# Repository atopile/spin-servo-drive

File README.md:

# Servos are dope.

Compared to the steppers we stick on our 3D printers, CNC machines and paintball turrets:
 - They're way faster 🏃
 - Far more powerful (higher torque for longer) 💪
 - More accurate (higher resolution) 🎯
 - And they're closed loop (they know where they are) 🤖

The only downside is that they're expensive, like hundreds of dollars.

Introducing spin ✨ - the $30 servo for the masses (designed with atopile)

## Wiggle wiggle wiggle

## Build your own Spin Servo Motor Drive

This project is fully open source and designed with [atopile](https://github.com/atopile/atopile), a new language and compiler to design electronics with code.

## Goals + (default) Specs

- Obviously better option than stepper motors for 3D printers, CNC machines and robotics
- Open-source design that is easy to:
  - contribute to
  - fork maintainable derivatives of
  - robust

- 2x CAN comms with JST-GH connectors
- XT30 power connector
- 0.25Nm continuous rated torque (0.75Nm peak)
- <0.1° resolution
- 12V-24V input voltage

## Getting started

This project was written in `ato`, a new electronics description language we are developing to help create and share electronic designs. Get started here: https://atopile.io/

### Electronics

**Write me please!**

### Firmware

Install [PlatformIO](https://platformio.org/) into VSCode. It has the utilities to build, upload and debug the firmware.

You may also need to install `libusb` (eg. `brew install libusb` on OSx) to run the build!

There are a few build configurations:
- `debug` is intended as a JTAG configuration and includes symbols to run the debugger.
- `dfu-manual` uses the GNU command-line dfu-utility to trigger the upload via USB (**Recommended USB workflow**)
- `dfu` uses the built-in PlatformIO dfu utility to program via USB (which **I struggled with on OSx**)

To run a build either use the sidebar (easiest IMO) or PlatformIO CLI (`pio run --help`).

#### Side-bar

#### CLI

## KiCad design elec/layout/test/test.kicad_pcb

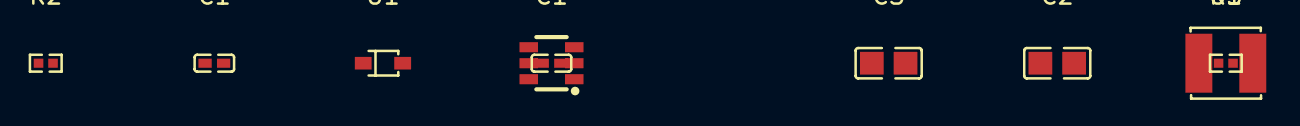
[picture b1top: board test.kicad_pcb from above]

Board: 2 copper layers, 9 parts (0 on the bottom side), 7 nets, no tracks yet.

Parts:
C1: 1µF ±10% 25V X5R; C0402-b3ef17
C1#2: 470nF ±20% 16V X5R; C0402-b3ef17
C2, C3: 10µF ±10% 25V X5R; C0805-3b2e55
R1: 7.5kΩ ±1% 62.5mW; R0402-56259e
R2: 24kΩ ±1% 62.5mW; R0402-56259e
U1: SOD-323_L1.8-W1.3-LS2.5-RD
U2: SOT-23-6_L2.9-W1.6-P0.95-LS2.8-BR
U3: 10µH ±20%; IND-SMD_L4.0-W4.0

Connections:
CB: C1#2.1, U2.1
cathode: C1#2.2, U1.1, U2.6, U3.1
gnd: C2.2, U2.2
gnd-1: C3.2, R1.2, U1.2
hv: C2.1, U2.4, U2.5
hv-1: C3.1, R2.1, U3.2
line: R1.1, R2.2, U2.3

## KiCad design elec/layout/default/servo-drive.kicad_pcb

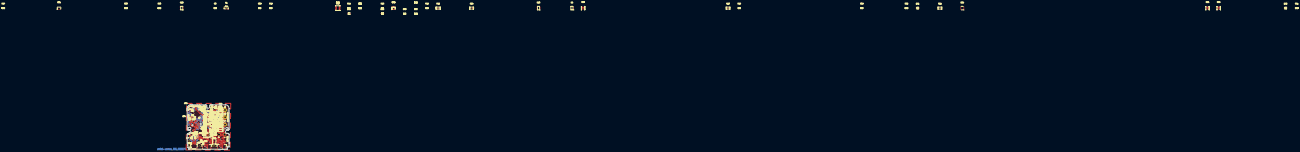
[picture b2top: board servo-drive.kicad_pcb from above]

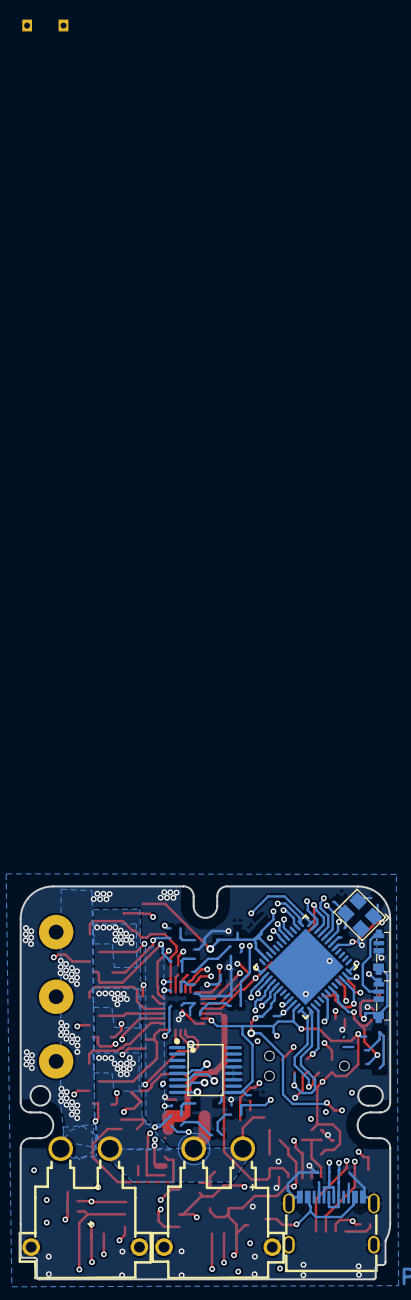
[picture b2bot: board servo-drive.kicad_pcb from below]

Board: 4 copper layers, 37.6 x 39.9 mm, 138 parts (8 on the bottom side), 80 nets.

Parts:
C2, C13, C16, C17, C18, C19, C28, C40, C51: 100nF ±10% 16V X7R; C0402-b3ef17
C3, C4, C6, C20, C21, C22, C25, C26, C27, C29, C30, C35, C36, C37, C38, C39, C47, C48, C49: 10µF ±10% 50V X5R; C0805-3b2e55
C7, C33, C34, C41, C43, C45, C50: 1µF ±10% 16V X5R; C0402-b3ef17
C10, C11, C12: 2.2nF ±10% 50V X7R; C0402-b3ef17
C23, C31, C32: 4.7µF ±10% 16V X5R; C0603-bd72f6
C42, C44: 20pF ±5% 50V C0G; C0402-b3ef17
DS1, DS2: Diode_1N5819WS; SOD-323_L1.8-W1.3-LS2.5-RD
DS1#2, DS2#2: SOD-323_L1.8-W1.3-LS2.5-RD
J1: USB-C-SMD_KH-TYPE-C-16P
R1, R10, R11, R15, R16, R20, R38, R46, R52: 10kΩ ±1% 62.5mW; R0402-56259e
R2, R6, R13, R25, R44, R48, R50: 1kΩ ±1% 62.5mW; R0402-56259e
R3: 100kΩ ±1% 62.5mW; R0402-56259e
R5, R9: 5.1kΩ ±1% 62.5mW; R0402-56259e
R7: 200Ω ±1% 62.5mW; R0402-56259e
R12, R14, R26, R45, R49, R51: 45.3kΩ ±1% 62.5mW; R0402-56259e
R31: 40.2kΩ ±1% 62.5mW; R0402-56259e
U1: KEY-SMD_SKTDLDE010
U2, U14: CONN-TH_XT30PW-M
U3: 10kΩ ±1% 62.5mW; R0402-56259e
U4, U6, U20, U23: SOT-23-5_L3.0-W1.7-P0.95-LS2.8-BR
U5, U32: LED-SMD_4P-L4.0-W1.4_SK6805SIDE-S
U7, U8, U9: OutputPad
U10, U21, U24: _DMT3009LDT_7; V-DFN3030-8K_L3.0-W3.0-P0.65-BL
U10#2, U21#2, U24#2: 3mΩ ±1% 500mW; R0805-c79e8b
U11, U22, U28: V-DFN3030-8K_L3.0-W3.0-P0.65-BL
U12: VQFN-24_L4.0-W4.0-P0.50-TL-EP2.5
U13: UFQFPN-48_L7.0-W7.0-P0.50-BL-EP
U15: CONN-SMD_4P-P1.00_SM04B-SRSS-TB-LF-SN
U16: TAG-CONNECT_TC2050-IDC
U17, U19, U31, U33, U34, U35: NetTie-2_SMD_Pad0.25mm
U18, U39: SOT-23-6_L2.9-W1.6-P0.95-LS2.8-BR
U25: SOIC-8_L4.9-W3.9-P1.27-LS6.0-BL
U26, U27: CONN-SMD_4P-P1.25_SM04B-GHS-TB-LF-SN
U29: TSSOP-16_L5.0-W4.4-P0.65-LS6.4-BL
U30: 470nF ±20% 16V X5R; C0402
U30#2: 470nF ±20% 16V X5R; C0402-b3ef17
U36, U38#2, U43#2, U44, U48, U49#2: 1kΩ ±1% 62.5mW; R0402-56259e
U37: OSC-SMD_4P-L3.2-W2.5-BL
U38, U43, U49: 10kΩ ±1% 62.5mW; R0402
U40: IND-SMD_L4.0-W4.0
U41: 4.7µF ±20% 6.3V X5R; C0402
U41#2: 2.2µF ±20% 6.3V X5R; C0402-b3ef17
U42: 10µF ±10% 25V X5R; C0805-3b2e55
U45, U47, U50#2, U52#2: 1µF ±10% 16V X5R; C0402-b3ef17
U46: _LDK220M_R; SOT-23-5_L3.0-W1.7-P0.95-LS2.8-BL
U46#2, U51: SOT-23-5_L3.0-W1.7-P0.95-LS2.8-BL
U50, U52: 1µF ±10% 16V X5R; C0402

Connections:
A5: J1.A5, R5.1
ADJ_NC: U48.1, U49#2.2, U51.4
B5: J1.B5, R9.1
CANH: U25.7, U26.2, U27.2
CANL: U25.6, U26.3, U27.3
CB: U30#2.1, U39.1
FB: U36.1, U38#2.2, U39.3
PF1_OSC_OUT: R7.1, U13.6
anchor: U1.3, U1.4
anode: DS2#2.2, J1.A4, J1.A9, J1.B4, J1.B9
cathode: DS1.1, DS1#2.1, U30.2, U30#2.2, U39.6, U40.1
cs: U13.25, U29.8
dm: J1.A7, J1.B7, U13.33
dp: J1.A6, J1.B6, U13.34
gnd: R26.2, R46.1, U20.4
gnd-1: R14.2, R45.2, R51.2, U4.3, U4.4
gnd-2: C2.2, C3.2, C4.2, C6.2, C7.2, C10.2, C11.2, C12.2, C13.2, C16.2, C17.2, C18.2, C19.2, C20.2, C21.2, C22.2, C23.2, C25.2, C26.2, C27.2, C28.2, C29.2, C30.2, C31.2, C32.2, C33.2, C34.2, C35.2, C36.2, C37.2, C38.2, C39.2, C40.2, C42.2, C44.2, C47.2, C48.2, C49.2, C50.2, C51.2, DS1.2, DS1#2.2, J1.1, J1.2, J1.3, J1.4, J1.A1, J1.A12, J1.B1, J1.B12, R2.2, R5.2, R9.2, R11.2, R20.1, R31.2, R38.2, U2.1, U2.3, U2.4, U3.2, U4.2, U5.2, U6.2, U10#2.2, U12.6, U12.25, U13.49, U14.1, U14.3, U14.4, U15.1, U15.5, U15.6, U16.3, U16.5, U18.2, U19.2, U20.2, U21#2.2, U23.2, U24#2.2, U25.2, U25.8, U26.4, U26.5, U26.6, U27.4, U27.5, U27.6, U29.4, U29.11, U29.12, U29.13, U32.2, U33.2, U35.2, U36.2, U37.2, U37.4, U39.2, U41.2, U41#2.2, U42.2, U43.2, U43#2.2, U45.2, U46.2, U46#2.2, U47.2, U48.2, U50.2, U50#2.2, U51.2, U52.2, U52#2.2
gnd-3: U10#2.1, U11.5, U11.6, U11.7, U17.2
gnd-4: R49.2, R52.1, U23.4
gnd-5: R12.2, R16.1, U6.4
gnd-6: U21#2.1, U22.5, U22.6, U22.7, U31.2
gnd-7: U24#2.1, U28.5, U28.6, U28.7, U34.2
hv: C7.1, C13.1, C16.1, C17.1, C18.1, C40.1, C50.1, C51.1, R1.1, R3.2, R15.1, U1.2, U4.5, U6.5, U12.5, U13.20, U13.21, U13.23, U13.35, U13.48, U15.2, U16.1, U18.5, U20.5, U23.5, U25.3, U29.9, U44.1, U46#2.5, U47.1
hv-1: C3.1, C4.1, C6.1, C20.1, C21.1, C22.1, C25.1, C26.1, C27.1, C29.1, C30.1, C35.1, C36.1, C37.1, C38.1, C39.1, C47.1, C48.1, C49.1, R10.1, U2.2, U11.2, U11.3, U11.4, U11.10, U14.2, U22.2, U22.3, U22.4, U22.10, U28.2, U28.3, U28.4, U28.10, U39.4, U39.5, U41#2.1
hv-2: C23.1, C31.1, C32.1, U12.4, U38#2.1, U40.2, U42.1, U50#2.1, U51.1, U51.3
hv-3: C33.1, C34.1, DS2#2.1, U5.1, U10.2, U10.3, U10.4, U10.10, U21.2, U21.3, U21.4, U21.10, U24.2, U24.3, U24.4, U24.10, U26.1, U27.1, U32.1, U41.1, U45.1, U46#2.1, U46#2.3, U49#2.1, U51.5, U52#2.1
inverting: R6.2, R12.1, U6.3
inverting-1: R48.2, R49.1, U23.3
inverting-2: R25.2, R26.1, U20.3
io: C28.1, R15.2, U3.1, U13.12
io-1: U12.10, U22.8
io-2: C43.2, U8.1, U12.15, U22.9
io-3: U12.1, U12.22, U13.8
ios-io: U5.3, U32.4
micro-io: R2.1, U13.46, U18.4
micro-io-2: R3.1, U13.14, U18.6
miso: U13.27, U29.5
mosi: U13.28, U29.6
non_inverting: C2.1, R1.2, R38.1, U4.1
non_inverting-1: R13.2, R14.1, U6.1
non_inverting-2: R44.2, R45.1, U20.1
non_inverting-3: R50.2, R51.1, U23.1
out: U43#2.1, U44.2, U46#2.4
power_stage.gate_driver-io: C45.1, U12.14
power_stage.gate_driver-io-1: R31.1, U12.21
power_stage.gate_driver-vcc: C43.1, U12.17
power_stage.gate_driver-vcc-1: C41.1, U12.20
power_stage.phase_a.current_sensor-top: R13.1, U17.1
power_stage.phase_a.current_sensor-top-1: R6.1, U19.1
power_stage.phase_b.current_sensor-top: R25.1, U33.1
power_stage.phase_b.current_sensor-top-1: R44.1, U31.1
power_stage.phase_c.current_sensor-top: R50.1, U34.1
power_stage.phase_c.current_sensor-top-1: R48.1, U35.1
reset: U13.7, U16.10
rx: U18.3, U25.4
sck: U13.26, U29.7
scl: U13.16, U15.4
sda: U13.30, U15.3
tck: U13.37, U16.4
tdi: U13.38, U16.8
tdo: U13.41, U16.6
tms: U13.36, U16.2
tx: U13.47, U25.1
vcc: U12.9, U28.8
vcc-1: U12.3, U12.24, U13.10
vcc-2: C41.2, U7.1, U11.9, U12.18
vcc-3: C12.1, R52.2, U13.11
vcc-4: U11.1, U12.19
vcc-5: U12.16, U22.1
vcc-6: U12.13, U28.1
vcc-7: U11.8, U12.11
vcc-8: C10.1, R16.2, U10.9, U13.17
vcc-9: R20.2, U1.1, U13.43, U18.1
vcc-10: C11.1, R46.2, U13.18
vcc-11: U12.2, U12.23, U13.9
vcc-12: C45.2, U9.1, U12.12, U28.9
vcc-13: C19.1, R10.2, R11.1, U13.13
vcc-14: U5.4, U13.29
xin: C42.1, U13.5, U37.1
xout: C44.1, R7.2, U37.3

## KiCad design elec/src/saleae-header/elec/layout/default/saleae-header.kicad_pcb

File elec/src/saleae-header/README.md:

# template

Project description goes here.

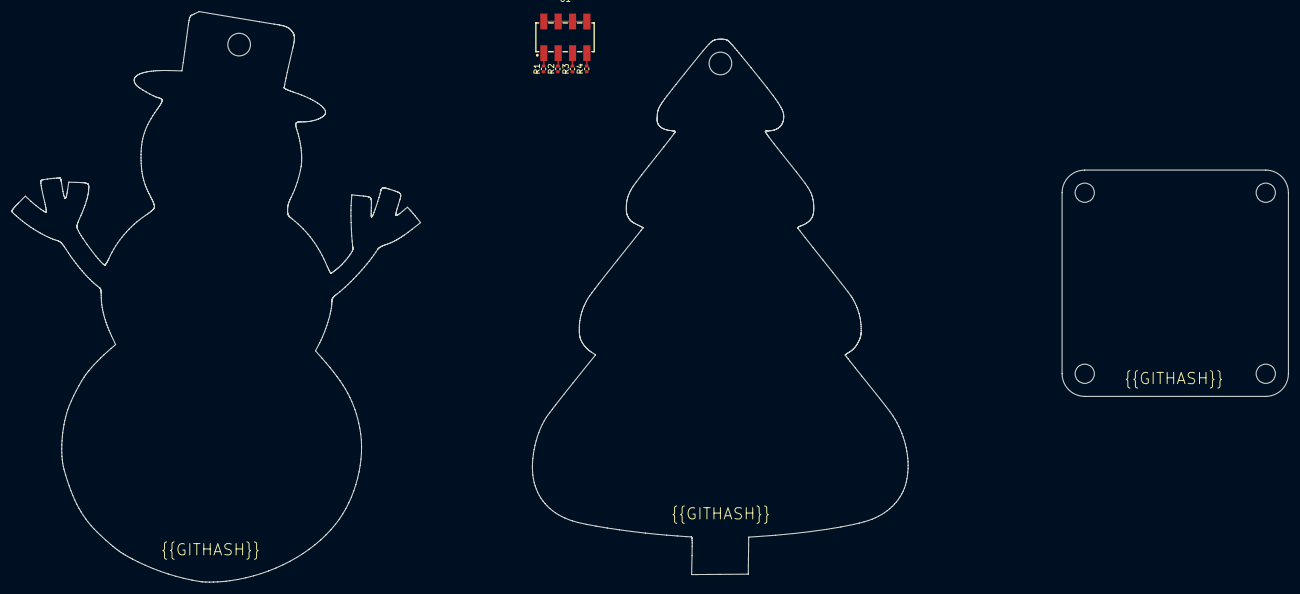
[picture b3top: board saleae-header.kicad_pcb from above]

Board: 2 copper layers, 66.4 x 94.6 mm, 5 parts (0 on the bottom side), 5 nets.

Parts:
R1, R2, R3, R4: Chip Resistor - Surface Mount 1KOhms ±5% 1/16W 04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; R0402
U1: HDR-SMD_8P-P2.54-V-M-R2-C4-LS7.4

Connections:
_1: R1.2, U1.1
_3: R2.2, U1.3
_5: R3.2, U1.5
_7: R4.2, U1.7
gnd: U1.2, U1.4, U1.6, U1.8

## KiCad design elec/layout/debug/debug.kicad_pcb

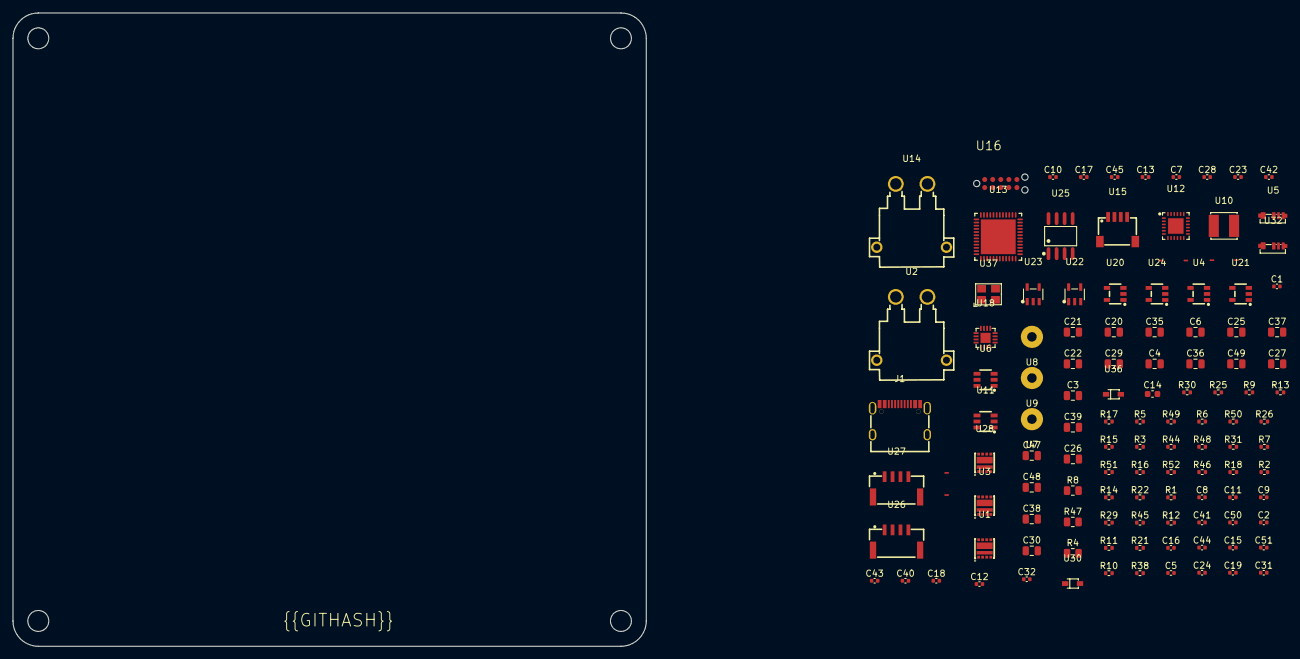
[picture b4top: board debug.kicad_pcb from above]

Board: 2 copper layers, 100.0 x 100.0 mm, 120 parts (0 on the bottom side), 75 nets, no tracks yet.

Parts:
C1, C5, C9, C15, C16, C18, C28, C31, C32, C41, C43, C45, C50: 25V 1uF X5R ±10% 0402 Multilayer Ceramic Capacito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; C0402
C2, C7, C13, C17, C19, C23, C40, C51: 16V 100nF X7R ±10% 0402 Multilayer Ceramic Capaci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; C0402
C3, C4, C6, C20, C21, C22, C25, C26, C27, C29, C30, C35, C36, C37, C38, C39, C47, C48, C49: C0805
C8: 6.3V 10uF X5R ±20% 0402 Multilayer Ceramic Capaci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; C0402
C10, C11, C12: 50V 2.2nF X7R ±10% 0402 Multilayer Ceramic Capaci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; C0402
C14: 50V 1uF X5R ±10% 0603 Multilayer Ceramic Capacito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; C0603
C24: 16V 220nF X7R ±10% 0402 Multilayer Ceramic Capaci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; C0402
C42, C44: 50V 20pF C0G ±5% 0402 Multilayer Ceramic Capacito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; C0402
J1: USB-C-SMD_KH-TYPE-C-16P
R1, R10, R11: 62.5mW ±1% ±200ppm/℃ 1.62kΩ 0402 Chip Resistor - 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; R0402
R2, R6, R13, R25, R44, R48, R50: 62.5mW Thick Film Resistors ±100ppm/℃ ±1% 1kΩ 040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; R0402
R3: 62.5mW Thick Film Resistors ±100ppm/℃ ±1% 100kΩ 0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; R0402
R4, R8, R47: R0805
R5, R9: 62.5mW Thick Film Resistors ±100ppm/℃ ±1% 5.1kΩ 0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; R0402
R7: 62.5mW Thick Film Resistors ±100ppm/℃ ±1% 220Ω 04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; R0402
R12, R14, R26, R45, R49, R51: 62.5mW Thick Film Resistors ±100ppm/℃ ±1% 47kΩ 04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; R0402
R15: 62.5mW Thick Film Resistors ±100ppm/℃ ±1% 10kΩ 04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; R0402
R16, R46, R52: 62.5mW ±1% ±200ppm/℃ 73.2Ω 0402 Chip Resistor - S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; R0402
R17: 62.5mW Thick Film Resistors ±100ppm/℃ ±1% 20.5kΩ 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; R0402
R18: 62.5mW Thick Film Resistors ±100ppm/℃ ±1% 6.34kΩ 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; R0402
R21: 62.5mW Thick Film Resistors ±100ppm/℃ ±1% 11.5kΩ 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; R0402
R22: 62.5mW Thick Film Resistors ±100ppm/℃ ±1% 6.19kΩ 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; R0402
R29: 62.5mW Thick Film Resistors ±100ppm/℃ ±1% 41.2kΩ 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; R0402
R30: 62.5mW Thick Film Resistors ±100ppm/℃ ±1% 4.32kΩ 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; R0402
R31: 62.5mW Thick Film Resistors ±100ppm/℃ ±1% 40.2kΩ 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; R0402
R38: 62.5mW Thick Film Resistors ±100ppm/℃ ±1% 1.54kΩ 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; R0402
U1, U3, U28: V-DFN3030-8K_L3.0-W3.0-P0.65-BL
U2, U14: CONN-TH_XT30PW-M
U4, U20, U21, U24: SOT-23-5_L3.0-W1.7-P0.95-LS2.8-BR
U5, U32: LED-SMD_4P-L4.0-W1.4_SK6805SIDE-S
U6, U11: SOT-23-6_L2.9-W1.6-P0.95-LS2.8-BR
U7, U8, U9: OutputPad
U10: IND-SMD_L4.0-W4.0
U12: VQFN-24_L4.0-W4.0-P0.50-TL-EP2.5
U13: UFQFPN-48_L7.0-W7.0-P0.50-BL-EP
U15: CONN-SMD_4P-P1.00_SM04B-SRSS-TB-LF-SN
U16: TAG-CONNECT_TC2050-IDC
U17, U19, U31, U33, U34, U35: NetTie-2_SMD_Pad0.25mm
U18: VQFN-16_L3.0-W3.0-P0.50-BL-EP1.6
U22, U23: SOT-23-5_L3.0-W1.7-P0.95-LS2.8-BL
U25: SOIC-8_L4.9-W3.9-P1.27-LS6.0-BL
U26, U27: CONN-SMD_4P-P1.25_SM04B-GHS-TB-LF-SN
U30, U36: SOD-323_L1.8-W1.3-LS2.5-RD
U37: OSC-SMD_4P-L3.2-W2.5-BL

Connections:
canh: U25.7, U26.2, U27.2
canl: U25.6, U26.3, U27.3
cb: C24.1, U6.1
cc1: J1.A5, R5.1
cc2: J1.B5, R9.1
cs: U13.25, U18.5
dm: J1.A7, J1.B7, U13.33
dp: J1.A6, J1.B6, U13.34
pf1_osc_out: R7.1, U13.6
reset: U13.7, U16.10
rx: U11.3, U25.4
spin.ios.led1-vcc: U5.3, U32.4
spin.ios.temperature_sense_filter-vcc-1: C23.1, R11.2
spin.ios.voltage_sense_filter-vcc-1: C19.1, R10.2
spin.micro-miso: U13.27, U18.7
spin.micro-mosi: U13.28, U18.4
spin.micro-sck: U13.26, U18.15
spin.micro-scl: U13.38, U15.4, U16.8
spin.micro-sda: U13.45, U15.3
spin.micro-vcc: U5.4, U13.29
spin.micro-vcc-1: R15.2, U11.1, U13.12
spin.micro.micro-io: R2.1, U11.4, U13.46
spin.micro.micro-io-1: R3.1, U11.6, U13.14
spin.micro.micro.ic-vcc-1: C42.1, U13.5, U37.1
spin.micro.tc2050-gnd: U16.3, U16.5
spin.power_stage-gnd: C1.2, C5.2, C7.2, C8.2, C13.2, C14.2, C15.2, C16.2, C17.2, C18.2, C28.2, C31.2, C40.2, C42.2, C44.2, C50.2, C51.2, R2.2, R3.2, R15.1, R18.2, R22.2, R30.2, R31.2, U1.5, U1.6, U1.7, U1.9, U2.1, U3.5, U3.6, U3.7, U3.9, U5.2, U6.2, U11.2, U13.49, U14.1, U15.1, U18.8, U18.10, U18.17, U22.2, U23.2, U25.2, U25.8, U26.4, U27.4, U28.5, U28.6, U28.7, U28.9, U32.2, U36.2, U37.2, U37.4
spin.power_stage-gnd-2: U20.2, U21.2, U24.2
spin.power_stage-vcc: U1.2, U1.3, U1.4, U1.10, U3.2, U3.3, U3.4, U3.10, U28.2, U28.3, U28.4, U28.10
spin.power_stage-vcc-2: U20.5, U21.5, U24.5
spin.power_stage.bulk_caps-gnd: C3.2, C4.2, C6.2, C20.2, C21.2, C22.2, C25.2, C26.2, C27.2, C29.2, C30.2, C35.2, C36.2, C37.2, C38.2, C39.2, C47.2, C48.2, C49.2
spin.power_stage.bulk_caps-vcc: C3.1, C4.1, C6.1, C20.1, C21.1, C22.1, C25.1, C26.1, C27.1, C29.1, C30.1, C35.1, C36.1, C37.1, C38.1, C39.1, C47.1, C48.1, C49.1
spin.power_stage.gate_driver-vcc-2: C41.2, U12.18
spin.power_stage.gate_driver-vcc-3: C43.2, U12.15
spin.power_stage.gate_driver-vcc-4: C45.2, U12.12
spin.power_stage.gate_driver.ic-gnd: U12.6, U12.25
spin.power_stage.gate_driver.ic-vcc-1: C41.1, U12.20
spin.power_stage.gate_driver.ic-vcc-2: C43.1, U12.17
spin.power_stage.gate_driver.ic-vcc-3: C45.1, U12.14
spin.power_stage.phase_a-vcc: U12.1, U12.22, U13.8
spin.power_stage.phase_a.current_sensor-gnd: C2.2, C9.2, R38.2, U4.2
spin.power_stage.phase_a.current_sensor-vcc: U4.1, U4.4
spin.power_stage.phase_a.current_sensor.bias_div-out: R13.2, R14.1
spin.power_stage.phase_a.current_sensor.feedback_div-out: R6.2, R12.1
spin.power_stage.phase_a.current_sensor.output_filter-vcc-1: C10.1, R16.2
spin.power_stage.phase_a.half_bridge-vcc: U12.19, U28.1
spin.power_stage.phase_a.half_bridge-vcc-1: U12.11, U28.8
spin.power_stage.phase_b-vcc: R31.1, U12.2, U12.23, U13.9
spin.power_stage.phase_b.current_sensor.bias_div-out: R44.2, R45.1
spin.power_stage.phase_b.current_sensor.feedback_div-out: R25.2, R26.1
spin.power_stage.phase_b.current_sensor.output_filter-vcc-1: C11.1, R46.2
spin.power_stage.phase_b.half_bridge-vcc: U1.1, U12.16
spin.power_stage.phase_b.half_bridge-vcc-1: U1.8, U12.10
spin.power_stage.phase_c-vcc: U12.3, U12.24, U13.10
spin.power_stage.phase_c.current_sensor.bias_div-out: R50.2, R51.1
spin.power_stage.phase_c.current_sensor.feedback_div-out: R48.2, R49.1
spin.power_stage.phase_c.current_sensor.output_filter-vcc-1: C12.1, R52.2
spin.power_stage.phase_c.half_bridge-vcc: U3.1, U12.13
spin.power_stage.phase_c.half_bridge-vcc-1: U3.8, U12.9
spin.power_stage.voltage_reference-vcc: C9.1, R1.1, U4.5
spin.power_stage.voltage_reference.opamp-inverting: C2.1, R1.2, R38.1, U4.3
spin.power_supply-gnd: J1.1, J1.2, J1.3, J1.4, J1.A1, J1.A12, J1.B1, J1.B12, R5.2, R9.2
spin.power_supply-vcc: C14.1, C24.2, U2.2, U6.4, U6.5, U14.2
spin.power_supply-vcc-1: J1.A4, J1.A9, J1.B4, J1.B9
spin.power_supply-vcc-2: C5.1, C8.1, C16.1, R29.1, U10.2, U22.1, U22.3, U23.1, U23.3
spin.power_supply-vcc-3: C28.1, C31.1, U5.1, U26.1, U27.1, U32.1
spin.power_supply-vcc-4: C1.1, C7.1, C13.1, C17.1, C18.1, C40.1, C50.1, C51.1, R21.1, U11.5, U13.21, U13.23, U13.35, U13.48, U15.2, U18.13, U23.5, U25.3
spin.power_supply.buck.feedback_div-out: R29.2, R30.1, U6.3
spin.power_supply.ldo3V3.feedback_div-out: R21.2, R22.1, U23.4
spin.power_supply.ldo5V-vcc: C15.1, R17.1, U22.5
spin.power_supply.ldo5V.feedback_div-out: R17.2, R18.1, U22.4
sw: U6.6, U10.1, U36.1
tck: U13.37, U16.4
tdo: U13.41, U16.6
tms: U13.36, U16.2
xout: C44.1, R7.2, U37.3

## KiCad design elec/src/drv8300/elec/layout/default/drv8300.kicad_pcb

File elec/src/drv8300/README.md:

# drv8300

Wooohooo a new package!

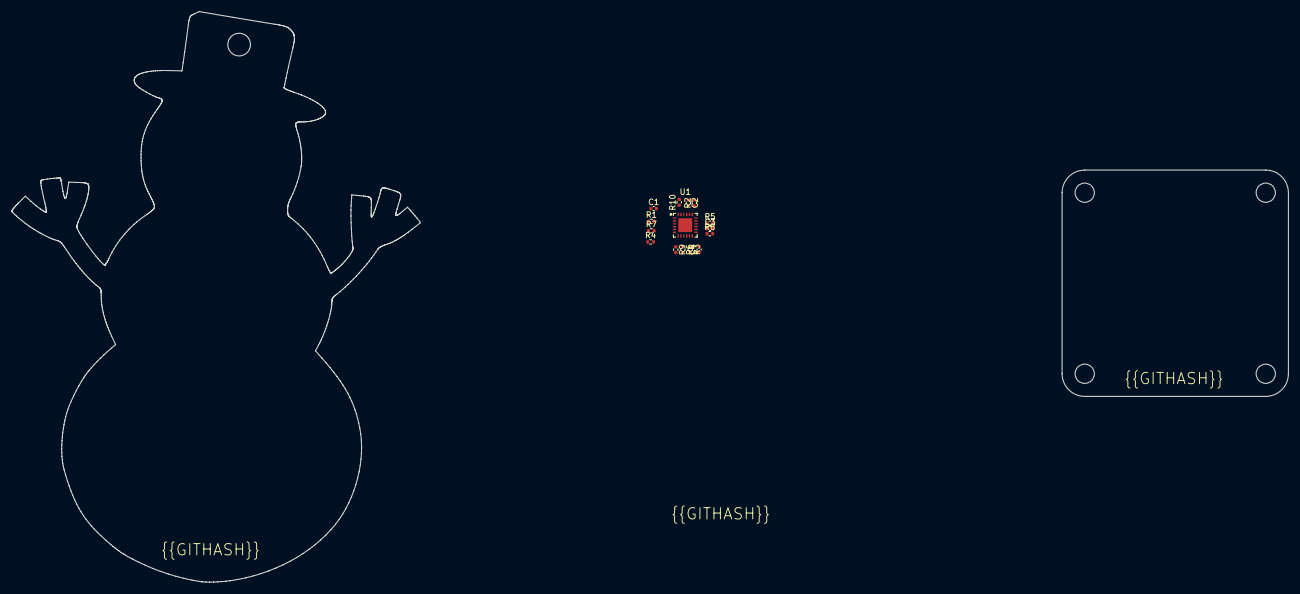
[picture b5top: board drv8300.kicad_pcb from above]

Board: 2 copper layers, 15 parts (0 on the bottom side), 15 nets, no tracks yet.

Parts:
C1, C2, C3, C4: 25V 1uF X5R ±10% 0402 Multilayer Ceramic Capacito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; C0402
R1, R4, R7: Chip Resistor - Surface Mount 4.7KOhms ±5% 1/16W 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; R0402
R2, R3, R5, R6, R8, R9: Chip Resistor - Surface Mount 10Ohms ±5% 1/16W 04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; R0402
R10: Chip Resistor - Surface Mount 39KOhms ±5% 1/16W 0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; R0402
U1: VQFN-24_L4.0-W4.0-P0.50-TL-EP2.5

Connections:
gnd: R1.2, R4.2, R7.2, R10.2, U1.6, U1.25
gnd-9: C2.2, C3.2, C4.2, U1.20
vcc-1: U1.4, U1.5
vcc-6: U1.1, U1.22
vcc-7: C2.1, U1.18
vcc-8: R2.1, R2.2, U1.19
vcc-9: R3.1, U1.11
vcc-13: R10.1, U1.2, U1.23
vcc-14: C3.1, U1.15
vcc-15: R5.1, R5.2, U1.16
vcc-16: R6.1, U1.10
vcc-20: U1.3, U1.24
vcc-21: C4.1, U1.12
vcc-22: R8.1, R8.2, U1.13
vcc-23: R9.1, U1.9

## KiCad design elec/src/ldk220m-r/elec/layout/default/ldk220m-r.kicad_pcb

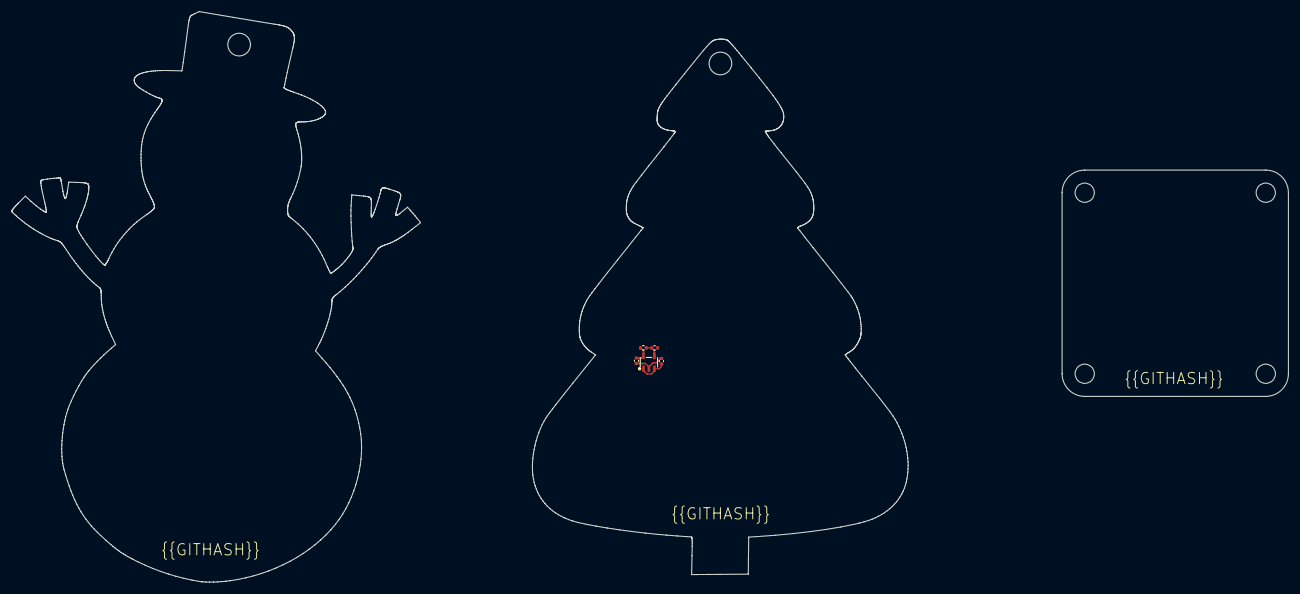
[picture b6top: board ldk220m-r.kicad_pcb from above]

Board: 2 copper layers, 66.4 x 94.6 mm, 5 parts (0 on the bottom side), 4 nets.

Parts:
C1, C2: Multilayer Ceramic Capacitors MLCC - SMD/SMT 1uF 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; C0402
R1: Chip Resistor - Surface Mount 18KOhms ±5% 1/16W 0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; R0402
R2: Chip Resistor - Surface Mount 10KOhms ±5% 1/16W 0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; R0402
U1: SOT-23-5_L3.0-W1.7-P0.95-LS2.8-BL

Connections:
gnd: C1.2, C2.2, R2.2, U1.2
out: R1.2, R2.1, U1.4
vcc: C1.1, U1.1, U1.3
vcc-1: C2.1, R1.1, U1.5

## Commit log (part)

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2023-06-04 repoint CI to all pcbdocs (no warranty on this one - it's completely untested)
2023-06-04 basic instructions on adding new components
2023-06-04 add base layout
2023-06-07 building components
2023-06-07 move footprint lib to generic 'lib'
2023-06-07 half bridge module
2023-06-08 current sensor and inital servoy connections
2023-06-14 finish half bridge module
2023-06-14 tidy old files
2023-06-14 finish current sense
2023-06-14 voltage reference
2023-06-14 move ref outside current sensor
2023-06-15 basic low pass filter
2023-06-17 Added differential input filtering
2023-06-17 hooking up at top level
2023-06-18 debug power stage written
2023-06-18 connect alternative gnds to pads
2023-06-18 add components and normalise footprints
2023-06-19 use commone designators and jlcpcb parts
2023-06-19 ato checks in CI
2023-06-19 hold the check builds - work out how to add atopile to that environment
2023-06-19 layout checkpoint 1
2023-06-21 layout done
2023-06-21 add githash to board
2023-06-28 connected pin 6 to output on L6387ED in HalfBridge Module
2023-06-28 Fixed current sensor not connected to ground issue
2023-07-08 init firmware platformio project
2023-07-08 blinky platformio project
2023-07-08 Motor's spinning baby!
2023-07-08 debugging sensor
2023-07-08 fix readme easyeda2kicad command
2023-07-08 add flash
2023-07-08 add switch
2023-07-08 add micro
2023-07-08 fix osc name
2023-07-08 fix switch name
2023-07-08 new build config
2023-07-08 fix osc component
2023-07-08 add vis config for visualizer
2023-07-08 Sensor worky
2023-07-08 shuffle things around
2023-07-08 create servo drive with micro
2023-07-08 connect the motor controller
2023-07-08 add sensor ato file, add v_sens, fix analog sens
2023-07-08 tidy up
2023-07-08 debug messages
2023-07-09 we're rolling with the offical release
2023-07-09 velocity tuning
2023-07-09 sensor and buck ready for review
2023-07-09 add vdiv rather than resistor. less lines, more readable
2023-07-09 add SGND signal for readability
2023-07-09 add diode
2023-07-09 add values to servo drive
2023-07-09 components
2023-07-09 added buck converter pad to PGND net
2023-07-09 vis updated for position sensor
2023-07-09 ready for review
2023-07-09 cleanup
2023-07-10 move vdiv to root src dir
2023-07-10 Make default build from servo_drive.ato
2023-07-10 tidy and... she builds
2023-07-10 split BoMs too
2023-07-10 allow check failures for now
2023-07-10 whoops, rename VdivFiltered
2023-07-10 split layouts - take 2
2023-07-10 generated designators
2023-07-10 move builds to root dir
2023-07-10 add USB footprints
2023-07-10 Fix VdivFiltered
2023-07-10 USB-C Lib Reference
2023-07-10 Spec LDO in BOM
2023-07-10 add rp2040 footprint
2023-07-10 import default-build netlist to KiCAD
2023-07-10 gnd on rp2040 footprint from JLCPCB is 57, not 0
2023-07-10 Hookup position sensor on default build
2023-07-10 Match RP2040 pinout with the debug config we brought up, but keep the analog inputs in the order that makes sense
2023-07-10 removed voltage sensors
2023-07-10 Connect vcc_3v3 to power_stage for voltage reference and current sense power
2023-07-10 Correct Buck-IC Package
2023-07-10 Connect 10v to power_stage for gate driver supply
2023-07-10 hook up micro power and ground
2023-07-10 Connect to USB on pico via inline resistors
2023-07-10 flipped pinout for a and c drives for nicer layout
2023-07-10 Make smaller output pads
2023-07-10 pad -> lib module lib name
2023-07-10 probably sleep deprived drivel
2023-07-12 component layout complete, fixed bug with CC2 pin and buck input cap gnd
2023-07-12 layout
2023-07-12 bug fixes
2023-07-12 added git hash
2023-07-13 more routing progress
2023-07-13 swap out current sense IC, reduce from 3 to 2, remove split reference opamp
2023-07-14 fix ad8418 name and vis locations
2023-07-14 change rc filter to output of amp, re-calculate shunt value and size
2023-07-14 add a bunch of visv2 settings
2023-07-16 Most DRC errors fixed
2023-07-17 Upgrade default layout paths
2023-07-18 typo
2023-07-19 Add ext_vcc signal and connect up to STEMMA QT connector
2023-07-21 Fix long-standing sytax error in ssms0402 file
2023-07-21 move stemma i2c to pins 10 and 11
2023-07-22 added LDO and led components
2023-07-23 fix the pin instantiation and signal naming
2023-07-23 flatten out file struct as interim fix
2023-07-26 minor improvement to stemma vis
2023-07-29 added adjustable LDO
2023-07-29 added LED to top level
2023-07-29 added enumeration switch
2023-07-29 GPIO25 is good for the LED
2023-07-29 fixed LED name for data input pin
2023-07-29 nitty tidy
2023-07-29 Fix build errors
2023-07-29 resolve all designators without clean
2023-07-29 Move STEMMA power input to 5V rather than 3v3
2023-07-29 Fix LED foorprint
2023-07-29 [fix] Phase-C was connected to the Phase-B output
2023-07-30 Added new dual fet package and wired up to half bridge module
2023-07-31 wired up current amp circuit
2023-07-31 wired up STM32, added in third current sensor
2023-07-31 lots of dumb little mistaktes
2023-08-01 fix bias on opamp for bidirectional sensing
2023-08-02 clean usbc for new vis language
2023-08-02 update positions, apply stubs
2023-08-06 initial component layout
2023-08-06 Add CAN stuffs
2023-08-07 library parts
2023-08-07 layout progress
2023-08-08 clean up designators for STM32 build
2023-08-08 general tidying as we go
2023-08-08 Specify cap size for the power-stage input bypass caps
2023-08-08 Placement 90% complete
2023-08-08 few bugs, ref shorted to 3v3 in servo drive, current sense not connected
2023-08-09 swapped out big boi caps for 0805s, finished most of the routing
2023-08-09 Fixed footprint for SK6805 LED, was a pain
2023-08-09 added JTAG with Tag connect interface, moved pos sensor to SPI2
2023-08-10 remove pulldowns, change gate drive to 0603
2023-08-10 fix SGND on exposed pad, join SGND to GND directly
2023-08-10 Revert "Merge branch 'jtuma/thermal-vias' into 'wire_up_stm32'"
    This reverts merge request !47
2023-08-11 layout improvements, well, getting there
2023-08-11 added some more caps, cleaned up layout
2023-08-12 swapped to cheaper buck
2023-08-12 renamed 10V rail
2023-08-12 via gun
2023-08-12 added JLCPNs
2023-08-14 Add BoM output to default build
2023-09-25 Remove designators prefixes
2023-09-30 Merge branch 'mawildoer/rejig-inheritance-structure' into 'develop/v1.1.0'
    Refactor existing top-level circuit design
    See merge request atopile/servo-drive!56
    (cherry picked from commit b7e7e3dd762b42cf0fcb014bbbeb24cab568bd95)
    8a86a514 WIP: Refactor existing top-level circuit design
    5f7c1039 Make L6387EDPowerStage compilable and make layout
    41acf5f1 Builds with v0.0.15 compiler
2023-09-30 address issues in #24
2023-09-30 missed one
2023-09-30 rename to stm32f103Cxxx
2023-10-01 Merge branch '25-create-drv8300-powerstage' into 'develop/v1.1.0'
    Create DRV8300 PowerStage and make default for NEMA-17 driver
    See merge request atopile/servo-drive!59
    (cherry picked from commit dc565ce4df3a3593bbe69c314f915e0b8032784e)
    6cb09225 Create DRV8300 Power Stage
    8dac7390 Switch out power stage at the top level
    620f2e74 Add basic rise rate tests
2023-10-01 Merge branch '27-add-jst-gh-2' into 'develop/v1.1.0'
    Add JST-GH
    See merge request atopile/servo-drive!63
    (cherry picked from commit ac3b010103b35113f3282bad606f9eae8ef2ad3c)
    0f95f9b4 add jst GH to lib
    4fed5fae add jst GH files
    afeed0dc fix blank space
2023-10-01 Stablise designators for v1.1.0
2023-10-05 add ato to readme
2023-10-05 Output from half bridge was not connected to output pad
2023-10-05 progress on layout
2023-10-12 bump rev requirement
2023-10-12 import new stm32 into layout
2023-10-17 updated tag connect pinout to work with the standard adapters
2023-10-17 fixed mistake + added source
2023-10-19 routing ~ half way done with DRV8300
2023-10-19 Added LED
2023-11-04 connected EP to GND on DRV8300
2023-11-05 big ol refactor, added lots of interfaces, changed pinout to match moteus controller, layout changed to add more connectors
2023-11-09 Modified micro pinout to match moteus, because they are pretty sick, updated modules to use interfaces where posible, generated netlist and imported to Kicad project
2023-11-10 fixed githash location, cleaned up silkscreen
2023-11-10 Minor silk fixes
2023-11-10 Add python ignores to firmware/.gitignore
2023-11-10 renamed step outputs to make Matt happy
2023-11-10 remove errant numbers excels
2023-11-11 fixing reset pin from PB4(TRST) to PG10_NRST
2023-11-11 added 100nf caps for current sense opamps
2023-11-11 cleaned up silk, missed some cheeky designators
2023-11-11 Use atopile-dev containers instead
2023-11-14 fixed via in pad issue + added signal names and test points for debugging
2023-11-14 remove old files and add new drawings + cad
2023-11-15 swapped out 0603 for 0402 component
2023-11-16 Revert "Use atopile-dev containers instead"
    This reverts commit 728492727da92ce9102edc28b09de52f8fe03426
2023-11-17 Move micro into sub-directory
2023-11-17 Update designators and UUIDs in layout
2023-11-23 Use generics resistors and caps instead of std lib
2023-11-23 Remove fp-lib-table from repo now that it's generated
2023-11-23 Up-rev modules
2023-11-27 Recursively clone submodulesg
2023-11-27 Use HTTPS clone of submodules
2023-11-27 Add dev container configuration
2024-01-24 remove vis files, update ato.yaml, remove ci
2024-01-24 update the microcontroller
2024-01-25 add regulators, usbc
2024-01-25 clean current sense
2024-01-25 add ci
2024-01-29 update power stage
2024-01-29 updated mpns
2024-01-31 Add settings.json to gitignore
2024-01-31 Use branch with additional interfaces for now on the STM32G4
2024-01-31 add pic
2024-02-01 fix led name
2024-02-02 relinked layout
2024-02-05 building locally
2024-02-19 top level refactor
2024-02-19 Add ato language spec
2024-02-19 refactor
2024-02-21 checkin
2024-02-21 micro pinout updates
2024-02-21 updating config
2024-02-23 add packages to platormio ini
2024-02-23 few tweaks
2024-03-07 fix typo in filter cutoff
2024-03-07 update deps
2024-03-08 Update platform reference
2024-03-08 WIP - bring up CAN
2024-03-12 Add multiplexer to boot pin
2024-03-12 add select resistor value and package + nits
2024-03-22 checkpoint
2024-03-22 checkpoint - linking correctly
2024-03-22 DRC fixes
2024-03-22 fix duplicate layout in packages
2024-03-22 remove debug build
2024-03-23 fix designators
2024-03-23 moving layout to correct folder
2024-04-06 current sense working
2024-04-11 added 3D step models
2024-04-16 adding step files for components
2024-04-16 removing unused debug config
2024-04-16 adding empty deps to ato.yaml
2024-05-02 swapping MA732 for MT6835 sensor
2024-05-02 adding step and wrl to gitattributes as binary files
2024-05-21 flip default select behaviour so button is driving PB8 on boot
2024-05-23 Flip connections around to follow logical flow
2024-05-23 Add assertions and equations to LowSideCurrentSense
2024-05-23 Increase allowed range for current feedback
2024-05-23 Flip net-ties to match improved flow
2024-05-24 Refactor power-stage to make it more reusable
2024-05-24 Move current sense feedback configuration outside default
2024-05-28 Add replacement notes to power-stage
2024-05-28 Flip shunts back around to match other layouts
2024-05-29 updating pinout to match board
2024-06-05 Add firmware upload docs
2024-06-05 update ci jobs
2024-06-05 update the readme with files
2024-06-05 remove test files
2024-06-05 Add download link for build artifacts (#32)
2024-06-20 updating pole pairs to 5
2024-06-24 updating resistance, kv and inductance
2024-07-09 Match datasheet pins on mux and rename to improve clarity on which is selected at any given time
2024-07-09 Remove duplicate file crud
2024-07-09 Fix package on buck.input_cap
2024-07-09 Update layout with pullup cap
2024-07-09 Remove trailing spaces
2024-07-09 Remove debug_builds dir from regular builds source code
2024-07-09 Re-add comments to platformio.ini
2024-07-09 Re-structure pio config to compose builds from multiple headlines
2024-07-09 Re-add lib README
2024-08-20 add function to read temp and limit based on temp
2024-08-28 adding 3d models
2024-10-08 fix naming
2024-12-13 Required changes for v0.3 compiler
2025-01-21 footprint not found issue
2025-02-06 update xt30 footprint to latest kicad version
2025-03-10 update CI job, remove regulator vendored packages and replace with linked installs of V3 parts
2025-03-10 refactor checkin, building up to solving
2025-03-11 fails when power interfaces are connected to regulator
2025-04-11 Make README assests static
2025-04-11 Update CI
